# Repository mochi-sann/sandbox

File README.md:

# sandbox

いろんなものを試しに書いてみるリポジトリです

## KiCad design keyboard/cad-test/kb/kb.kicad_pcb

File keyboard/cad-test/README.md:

# 18キー テストキーボード (kb)

XIAO RP2040 を使った 18 キーの自作キーボード。JLCPCB の 100×100mm 特価枠
(2層 5枚 $2) に収まるよう設計したテスト基板。

- レイアウト: 3行×5列 カラムスタッガー + 親指3キー
- 基板サイズ: **98.25 × 88.20 mm** (JLCPCB $2 枠内)
- マトリクス: 4行×5列、ダイオード COL2ROW (1N4148W, 裏面 SMD)
- スイッチ: Cherry MX 互換 + Kailh ホットスワップソケット (裏面)
- MCU: Seeed XIAO RP2040 (スルーホール実装、USB は基板左端)
- DRC / ERC: エラー 0 (KiCad 10, JLCPCB 2層ルール準拠)

## ファイル構成

| パス | 内容 |
|---|---|
| `kb/kb.kicad_pro` / `kb.kicad_sch` / `kb.kicad_pcb` | KiCad プロジェクト一式 (自己完結) |
| `kb/kb.kicad_sym` / `kb/local.pretty/` | プロジェクト内シンボル/フットプリント |
| `scripts/layout.py` | 単一のレイアウト定義 (キー座標・マトリクス・ピン割り当て) |
| `scripts/gen_sch.py` → `kb.kicad_sch` | 回路図の生成 |
| `scripts/gen_pcb.py` → `kb.kicad_pcb` | 部品配置と基板外形の生成 |
| `scripts/route.py` | 配線 (トラック/ビア) の生成 |
| `scripts/verify_netlist.py` | ネットリストと設計の照合 |
| `scripts/export_gerber.sh` → `out/kb-jlcpcb.zip` | ガーバー出力 |
| `firmware/code.py` | KMK ファームウェア (CircuitPython) |

再生成する場合は `gen_sch.py` → `gen_pcb.py` → `route.py` → `export_gerber.sh` の順。

## JLCPCB 発注手順 (基板のみ・最安構成)

部品は全部自分でハンダ付けするので、JLCPCB には**基板製造だけ**を頼む。

1. https://cart.jlcpcb.com/quote を開く
2. **Add gerber file** に `out/kb-jlcpcb.zip` をアップロード
3. 設定 (基本はデフォルトのままで $2 になる):
   - Layers: 2 / Dimensions: 自動認識 (98.25×88.2mm)
   - PCB Qty: **5**
   - PCB Thickness: 1.6mm / PCB Color: Green (緑以外は+$)
   - Surface Finish: HASL (with lead) ※無鉛にしたければ LeadFree HASL (+$)
   - Outer Copper Weight: 1oz
   - その他オプションはすべてデフォルト
4. **PCB Assembly はオフのまま** (部品実装は頼まない)
5. 配送: OCS NEP / Global Standard Direct 等の最安便を選択
6. 合計: 基板 $2 + 送料 $1.5〜8 程度

## 部品リスト (別途購入、概算)

| 部品 | 数量 | 参考単価 | 入手先の例 |
|---|---|---|---|
| Seeed XIAO RP2040 | 1 | ¥900 | 秋月電子、スイッチサイエンス |
| Kailh ホットスワップソケット (MX用) | 18 | ¥25 | 遊舎工房、TALP KEYBOARD |
| 1N4148W (SOD-123) | 18 | ¥3 | 秋月電子 (100個入 ¥300 など) |
| Cherry MX 互換キースイッチ | 18 | ¥60〜 | 遊舎工房、TALP、Amazon |
| キーキャップ (1U) | 18 | ¥30〜 | 同上 |
| ピンヘッダ 1×7 (2.54mm) | 2 | ¥30 | 秋月電子 |

合計 (スイッチ・キーキャップ込み): **3,500〜5,000 円程度** + 基板代

## 組み立て

1. **裏面**に 1N4148W をハンダ付け。カソード線 (パッケージの帯) を
   シルクの帯マークに合わせる
2. **裏面**にホットスワップソケットをハンダ付け
3. XIAO RP2040 をピンヘッダで表面に実装 (USB コネクタが基板左端を向く)
4. 表からスイッチをソケットに差し込む

## ファームウェア (KMK)

1. XIAO RP2040 の BOOT を押しながら USB 接続 → RPI-RP2 ドライブが出る
2. [CircuitPython の .uf2](https://circuitpython.org/board/seeeduino_xiao_rp2040/) をコピー
3. [KMK](https://github.com/KMKfw/kmk_firmware) の `kmk/` フォルダと
   `firmware/code.py` を CIRCUITPY ドライブにコピー
4. キーマップは `code.py` の `keyboard.keymap` を編集

## ピン割り当て

| 信号 | XIAO ピン | RP2040 GPIO |
|---|---|---|
| COL0〜COL4 | D0〜D4 | GP26, GP27, GP28, GP29, GP6 |
| ROW0〜ROW3 | D5〜D8 | GP7, GP0, GP1, GP2 |

D9, D10 は未使用 (将来の拡張用: ロータリーエンコーダ、LED など)。

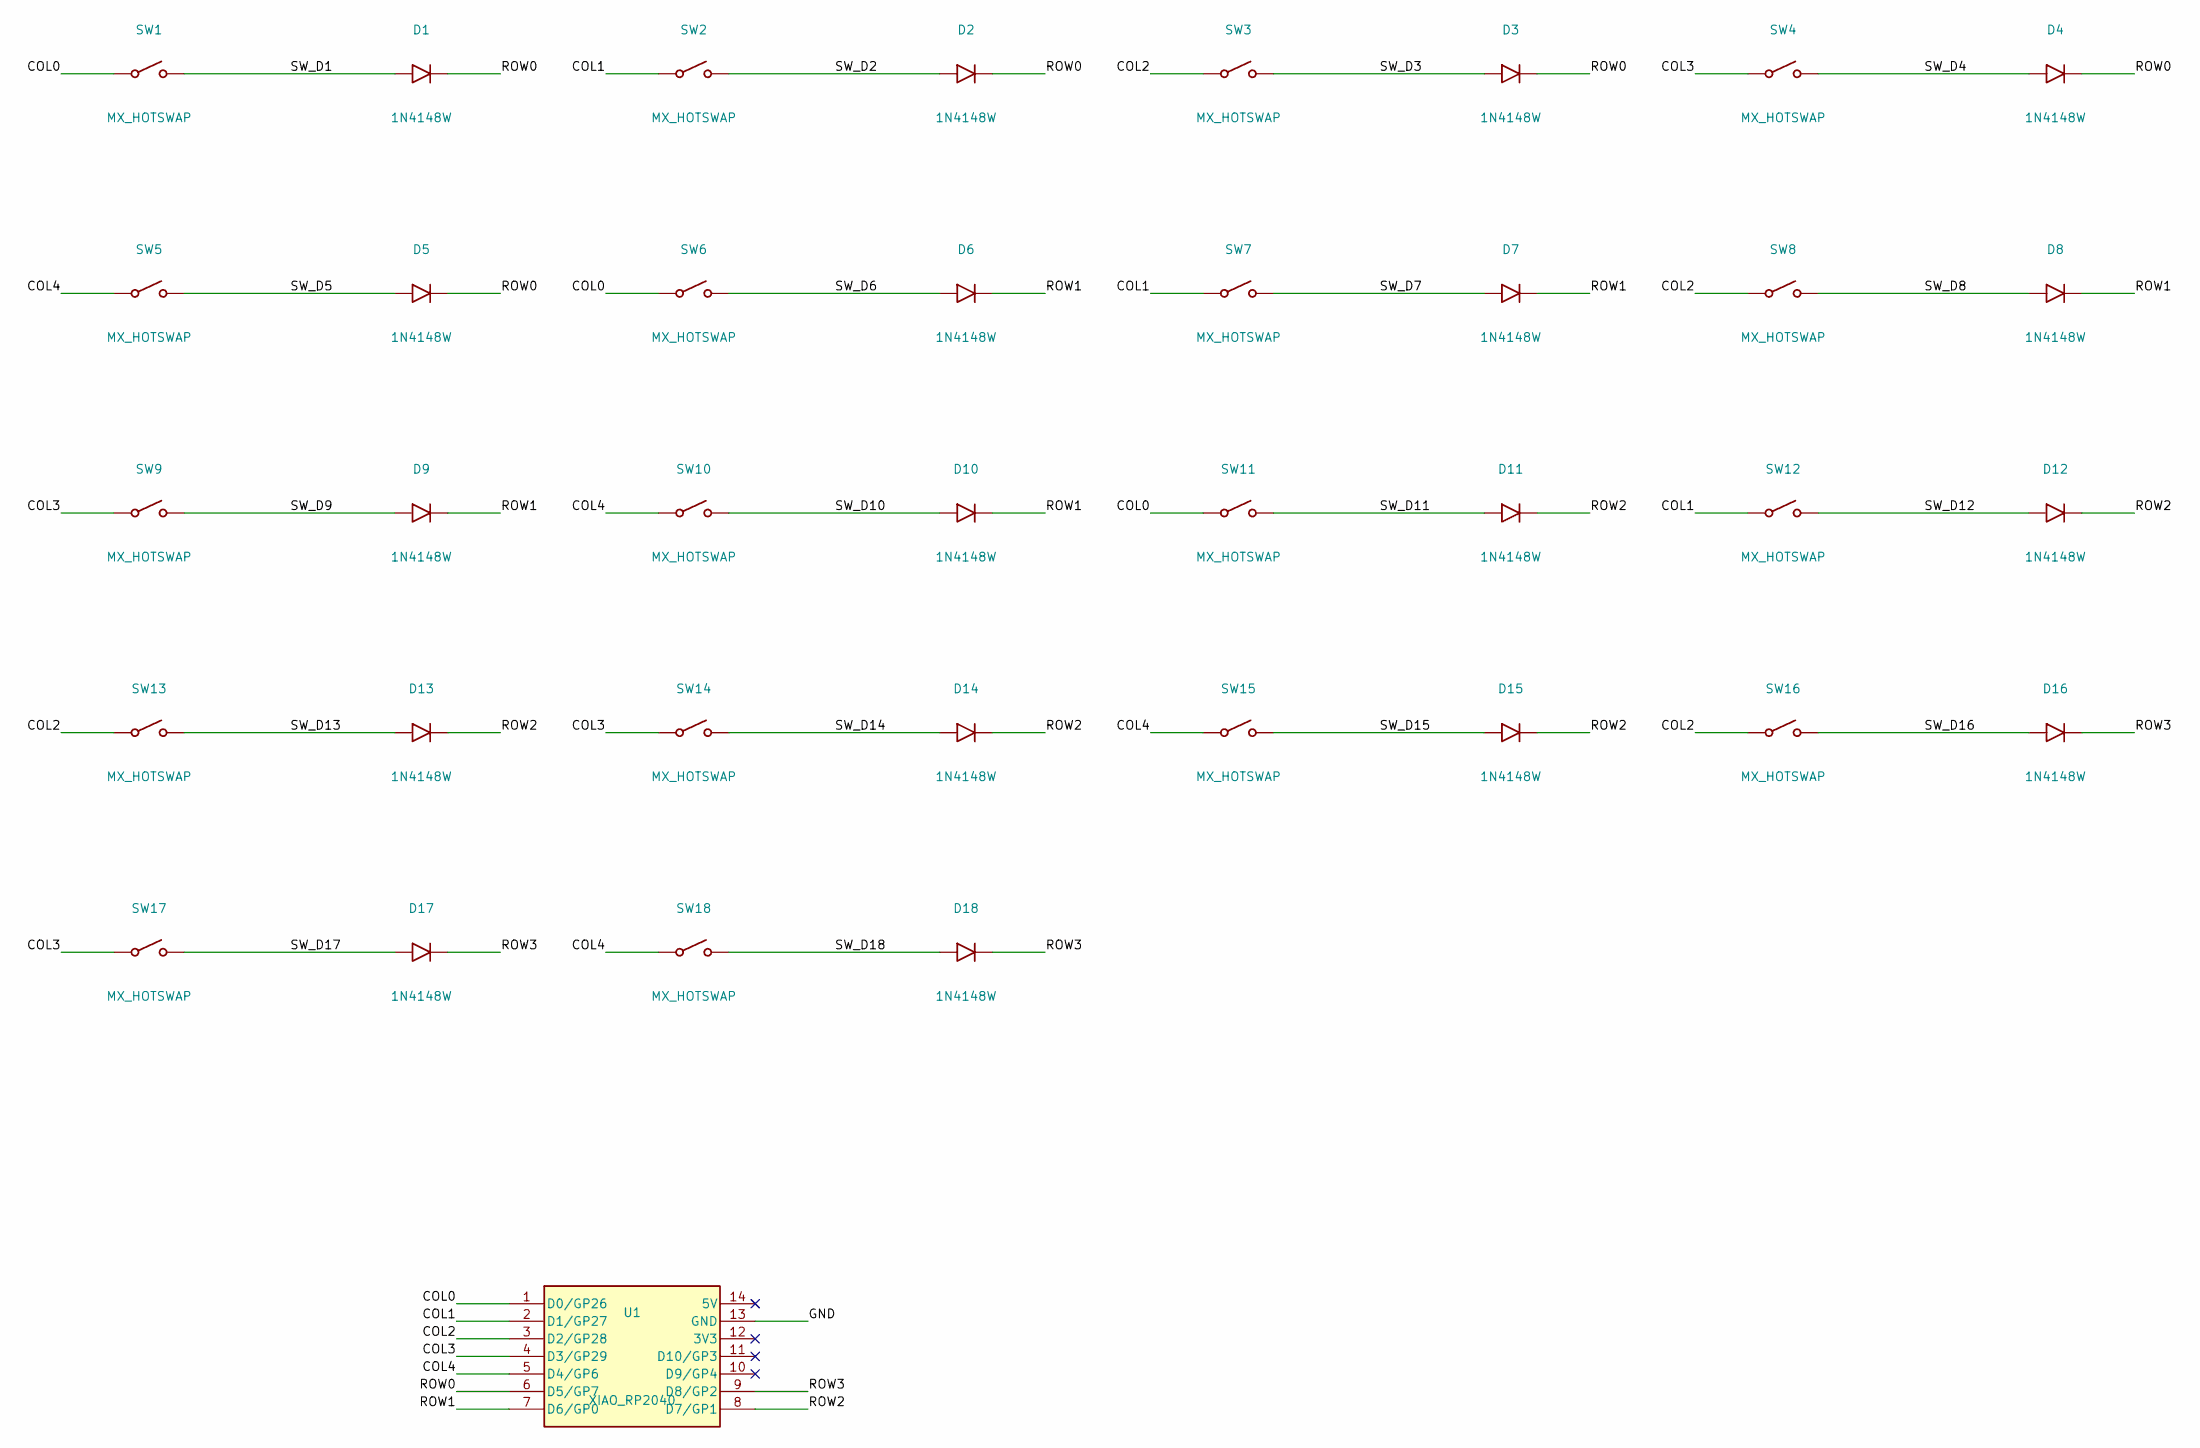
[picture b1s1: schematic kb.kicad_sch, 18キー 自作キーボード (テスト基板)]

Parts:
D1, D2, D3, D4, D5, D6, D7, D8, D9, D10, D11, D12, D13, D14, D15, D16, D17, D18: 1N4148W; D_SOD-123_HandSolder
SW1, SW2, SW3, SW4, SW5, SW6, SW7, SW8, SW9, SW10, SW11, SW12, SW13, SW14, SW15, SW16, SW17, SW18: MX_HOTSWAP; SW_Hotswap_Kailh_MX_1.00u
U1: XIAO_RP2040; XIAO-RP2040-DIP

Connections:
COL0: SW1.1, SW6.1, SW11.1, U1.1 (D0/GP26)
COL1: SW2.1, SW7.1, SW12.1, U1.2 (D1/GP27)
COL2: SW3.1, SW8.1, SW13.1, SW16.1, U1.3 (D2/GP28)
COL3: SW4.1, SW9.1, SW14.1, SW17.1, U1.4 (D3/GP29)
COL4: SW5.1, SW10.1, SW15.1, SW18.1, U1.5 (D4/GP6)
GND: U1.13 (GND)
ROW0: D1.1 (K), D2.1 (K), D3.1 (K), D4.1 (K), D5.1 (K), U1.6 (D5/GP7)
ROW1: D6.1 (K), D7.1 (K), D8.1 (K), D9.1 (K), D10.1 (K), U1.7 (D6/GP0)
ROW2: D11.1 (K), D12.1 (K), D13.1 (K), D14.1 (K), D15.1 (K), U1.8 (D7/GP1)
ROW3: D16.1 (K), D17.1 (K), D18.1 (K), U1.9 (D8/GP2)
SW_D1: D1.2 (A), SW1.2
SW_D2: D2.2 (A), SW2.2
SW_D3: D3.2 (A), SW3.2
SW_D4: D4.2 (A), SW4.2
SW_D5: D5.2 (A), SW5.2
SW_D6: D6.2 (A), SW6.2
SW_D7: D7.2 (A), SW7.2
SW_D8: D8.2 (A), SW8.2
SW_D9: D9.2 (A), SW9.2
SW_D10: D10.2 (A), SW10.2
SW_D11: D11.2 (A), SW11.2
SW_D12: D12.2 (A), SW12.2
SW_D13: D13.2 (A), SW13.2
SW_D14: D14.2 (A), SW14.2
SW_D15: D15.2 (A), SW15.2
SW_D16: D16.2 (A), SW16.2
SW_D17: D17.2 (A), SW17.2
SW_D18: D18.2 (A), SW18.2

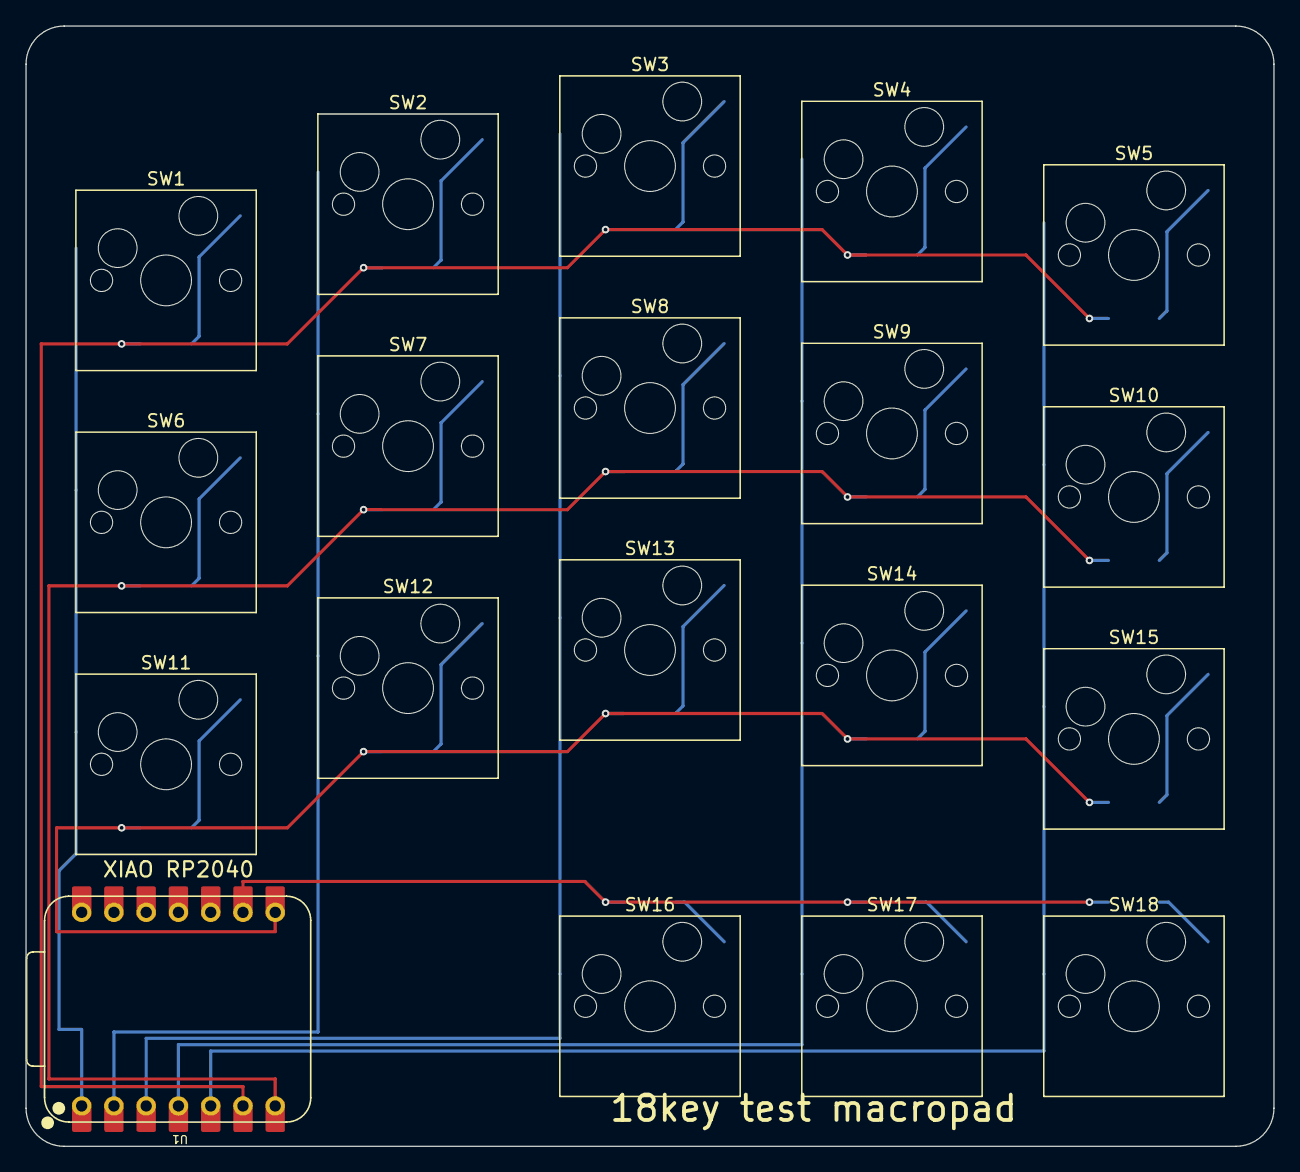
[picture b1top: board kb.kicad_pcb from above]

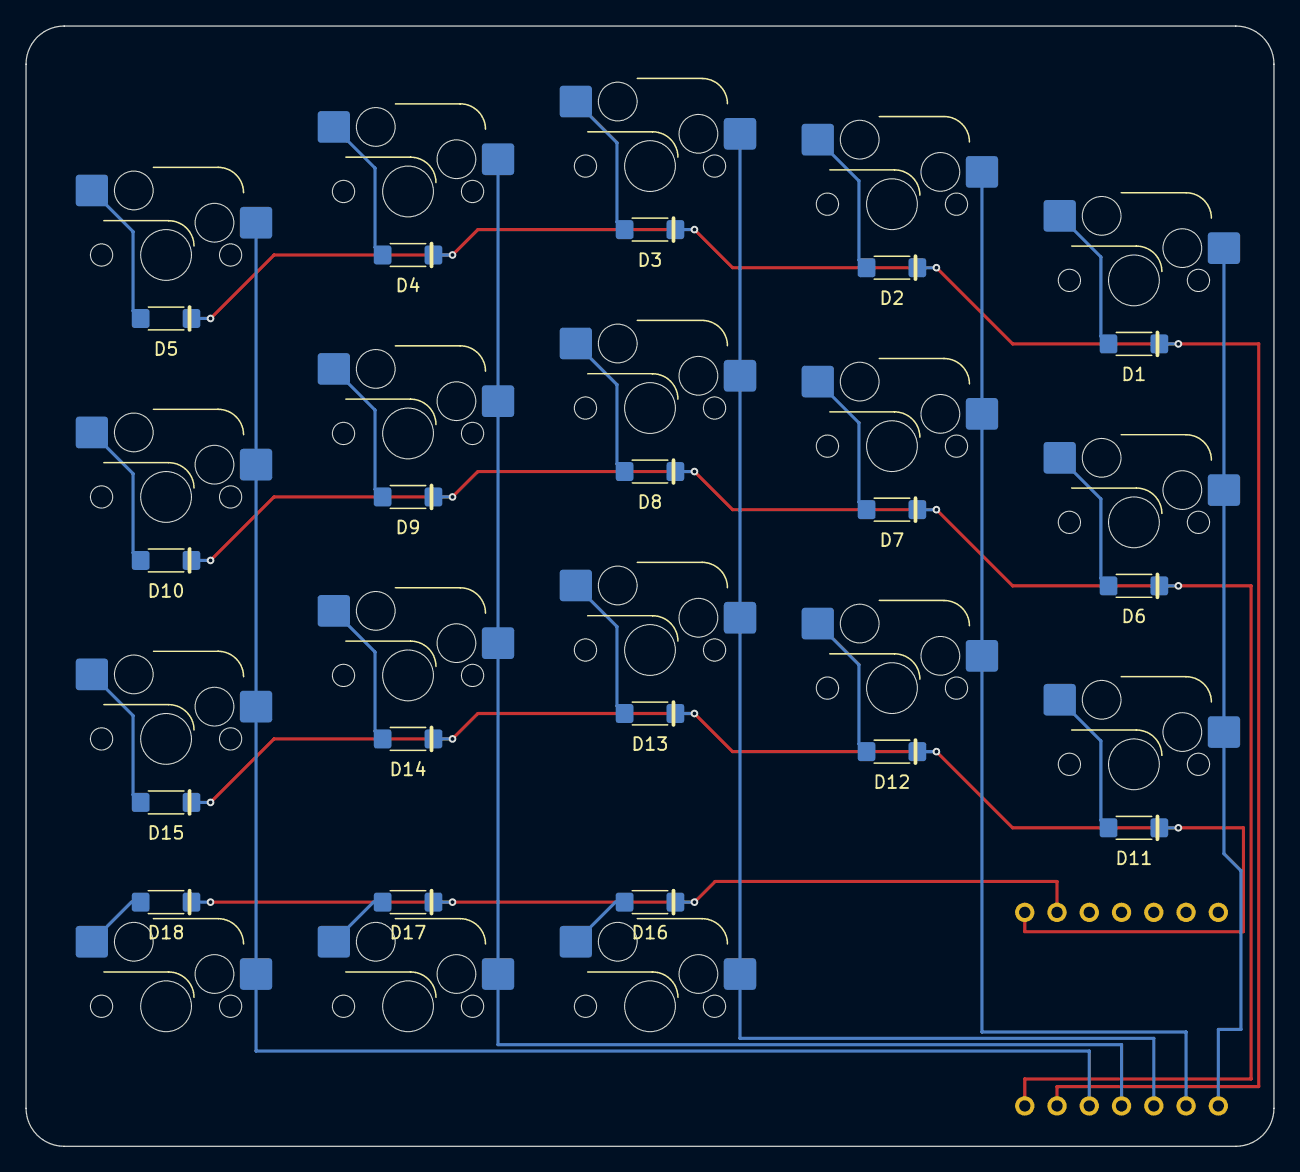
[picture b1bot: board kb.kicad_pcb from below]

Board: 2 copper layers, 98.2 x 88.2 mm, 37 parts (18 on the bottom side), 27 nets.

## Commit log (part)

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2023-02-17 tuika
2023-02-20 init
2023-02-20 heee
2023-02-22 hoge
2023-02-22 ファイルを分けた
2023-03-10 とりあえず動くようになった
2023-04-18 test-gpg
2023-04-21 aaaaa
2023-04-24 updatre
2023-05-07 add axum-hello
2023-05-09 set up prisma
2023-05-09 formatした
2023-05-09 色々追加
2023-05-16 dekita!!!!!!!!!!!!!!!
2023-05-16 iroiro shita
2023-05-23 hello world
2023-05-23 aaaaaaa
2023-05-23 upda
2023-05-26 hello
2023-06-02 upudate
2023-06-11 add icon folders
2023-09-03 udapte
2023-09-03 いろいろやった
2023-09-09 gpg test
2023-09-14 add sqlx
2023-09-16 run carg fix
2023-12-18 feat(create-turbo): apply package-manager transform
2023-12-18 feat(create-turbo): apply official-starter transform
2024-04-29 add udp
2024-04-29 update udp
2024-05-02 upcate
2024-05-14 add license.txt
2024-05-14 colorful-cubeをついか
2024-07-02 create gems
2024-07-09 add rails-docker
2024-08-15 update
    update
2024-09-01 dekita
2024-11-09 iroiro update
2024-12-04 add hono app
2024-12-04 add example
2024-12-04 update seed
2024-12-05 add view
2024-12-05 update prisma text case
2024-12-06 hoeg
2024-12-10 add adonijjs
2024-12-30 dneo
2024-12-30 udpate
2025-03-12 feat: Rails APIプロジェクトの初期設定を追加 新しいRails APIプロジェクトを作成し、必要なファイルと設定を追加して、開発環境を整備する。これにより、アプリケーションの開発がスムーズに進むようにする。
2025-03-12 feat: グループ管理機能を追加
    新しいGroupsControllerを作成し、グループのCRUD操作を実装する。
    Groupモデルとマイグレーションファイルを追加し、データベースにグループテーブルを作成する。
    テストファイルを追加して、グループ機能の動作を確認できるようにする。
2025-03-12 feat(Gemfile): rswagを追加してAPIドキュメント生成をサポート feat(initializers): Rswagの設定ファイルを追加 feat(routes.rb): Rswagのエンドポイントをルーティングに追加 feat(swagger_helper.rb): Swaggerドキュメントの設定を追加
2025-04-06 park ui init
2025-04-17 feat: Next.jsプロジェクトを新規作成し、基本設定を追加 新機能: .gitignore、README、ESLint、Next.js設定ファイルを追加 新機能: Tailwind CSSとTypeScriptの設定を追加 新機能: SVGアイコンとスタイルを含む基本的なページを作成
2025-04-17 feat: Todo編集フォームとサーバーアクションを追加 新機能: Todoを更新するためのフォームコンポーネントを作成し、サーバーアクションを実装
2025-04-19 feat: ReactとTypeScriptを使用したViteプロジェクトの初期設定を追加 新しいプロジェクトのために、React、TypeScript、Viteの設定ファイルと基本的な構成を作成し、ESLintの設定も含めた。
2025-04-19 feat: VueとReactの統合コンポーネントを追加 chore: .gitignoreに.aider*を追加 fix: App.tsxの構文エラーを修正 refactor: Viteの設定ファイルをTypeScriptからJavaScriptに変更
2025-05-30 修正(package.json): 不要な依存関係を削除し、新しい依存関係を追加 修正(App.tsx): BasicReactのインポートパスを修正 修正(BasicReact.jsx): Buttonコンポーネントのインポートを修正し、適切な関数を使用 修正(vite.config.js): Viteプラグインの設定を更新し、コメントを整理
2025-05-30 feat: TanStack Routerを使用した新しいプロジェクトを作成 新しいプロジェクトの初期設定を行い、ルーティング機能を追加。
2025-05-30 format
2025-06-26 kaizen
2025-06-26 iroirotuika
2025-10-08 add react
2025-11-29 test
2025-12-11 add t stack
2025-12-11 sakuzyo
2025-12-11 sugoi
2025-12-12 todoを更新
2025-12-12 openapiのスキーマと連携
2025-12-12 ログを改善
2025-12-12 テーマ切り替えを追加
2025-12-12 logを作った
2025-12-12 update project
2026-01-21 gameboy
2026-01-21 kannryou
2026-02-06 browser
2026-02-12 chore: checkpoint backgroaund_paths changes
2026-05-13 add 従量課金
2026-05-13 Build budget management MVP
2026-05-13 Handle invalid CSV rows safely
2026-05-13 Apply period granularity to analysis
2026-05-13 Refactor app into maintainable modules
2026-05-13 Switch to TanStack file based routing
2026-05-13 Lazy load file based routes
2026-05-13 Add audit previews filters and alerts
2026-06-20 マイクラっぽいものを作ってみた
